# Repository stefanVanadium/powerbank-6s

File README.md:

# powerbank-6s

A serious DIY power bank built around **six removable 18650 cells**. It's meant to last for years and charge a phone as fast as the wall charger does.

<p align="center"><sub>158.6 × 142.6 × 39.2 mm, milled 6061 aluminium with a polished front edge and a glass front: Qi2 ring and colour display under the glass, cell door with laser marking on the back.</sub></p>

## PCB Preview (4-Layer, 152 × 136 mm)

| Top — Power, PD/PPS, BMS & MCU | Bottom — 6× Removable 18650 Holders |
|---|---|
|  |  |

## Highlights

- **45W Super Fast Charging 2.0** for the Galaxy S24+ (USB PD 3.0 PPS), and **65W** for laptops
- **3x USB-C + 2x USB-A**. Each USB-C port has its own converter, so all of them work at full speed at the same time
- **Removable cells (6S1P)**: insert cells at any voltage, the BMS balances them, and you can pull them out fully charged
- **Pass-through charging**: one wall charger fills the pack and your phone overnight
- **Solar input**: plug a foldable USB-C panel into C1 (the charger tracks the panel's maximum power point)
- **Magnetic Qi2 wireless** charging under the glass front
- **Color display** showing every cell's voltage, watts in/out per port, and which slot has a problem
- **Real 6S BMS** with per-cell protection and balancing

## Enclosure (v1 model)

<p align="center"><sub>Rendered in Blender from the real model: the case parts from <code>enclosure/case.py</code> and the routed board exported from KiCad (<code>enclosure/blender_scene.py</code>).</sub></p>

| Front: glass, Qi2 ring, display, buttons | Back: cell door, logo, feet, port labels |
|---|---|
|  |  |

- **158.6 × 142.6 × 39.2 mm**, milled 6061 aluminium body (~290 g) + 2.5 mm aluminium cell door (~145 g)
- **Glass front**: one 1.5 mm tempered glass, black inside, with a window for the display; the Qi2 coil sits right under it (wireless charging can't pass through aluminium)
- **Aluminium mid-frame under the glass** doubles as the heat sink: thermal pads carry the heat from the 12 converter MOSFETs and 4 inductors into the frame and the walls. The case is sealed, with no vents
- **Cell door**: 4 Torx screws into steel hex standoffs that also hold the board, so swapping cells never wears the aluminium threads. Cell polarity and slot numbers are engraved inside the door
- Port openings follow the connector datasheets, with recesses for the plug overmolds and engraved labels
- Model in [build123d](https://github.com/gumyr/build123d) (`enclosure/case.py`), collision check against the real board (`enclosure/check.py`, 0 collisions), FreeCAD file `enclosure/out/powerbank_case.FCStd`

## How it works

```
USB-C1  in/out  ── TPS25751S ── BQ25756 ──┐
USB-C2  out     ── TPS25751S ── BQ25756 ──┤
USB-C3  out     ── TPS25751S ── BQ25756 ──┼── 6S removable pack ── BQ76952 BMS
USB-A1/A2 5V    ── LM73605 ──────────────┤
Qi2 module 12V  ── LMR36520 ─────────────┤
STM32G071 + TFT ── LMR36506 ─────────────┘
```

Each USB-C port pairs a TI PD controller with a BQ25756 bidirectional buck-boost, which produces any voltage from 3.3 to 21V in 20mV steps. That fine control is what PPS needs. An STM32 handles the display, splits the power budget between ports, and decides when the pack is full.

Full architecture, BOM with JLCPCB stock/prices, cost estimate and the cell-testing procedure are in **[powerbank.md](powerbank.md)**.

## Specs (planned)

| | |
|---|---|
| Cells | 6x 18650 in series, removable (currently EVE ICR18650/26V) |
| Pack | 15–25.2V, ~55Wh with 2.55Ah cells, ~75Wh with 3.5Ah cells |
| USB-C | 3 ports, PD 3.0 + PPS, up to 65W each |
| USB-A | 2 ports, 5V / 2A, BC1.2 |
| Wireless | Qi2 15W (module) |
| Input | USB-C PD or solar panel on C1 |
| Total output | ~100W from the pack, shared between ports |

## Repo layout

```
powerbank.md          project documentation (start here)
connections.md        safety Wave 0, power tree, I2C map, MCU pinout
powerbank.kicad_*     KiCad 10 project (6 hierarchical sheets + 4-layer PCB)
enclosure/            case model (build123d), collision check, FreeCAD file, STEP for milling
images/               3D PCB and case renders
lib/                  symbols, footprints, 3D models (verified against datasheets)
datasheets/           datasheets for every chosen part
powerbank.tex/.pdf    printable writeup
```

## Status

- [x] Requirements, architecture, full BOM & Safety Wave 0
- [x] KiCad libraries + datasheets + footprint audit
- [x] Schematic (6 hierarchical sheets, 241 components, 0 ERC errors)
- [x] PCB (4-layer 152 × 136 mm, 0 DRC violations, 0 unconnected pads)
- [ ] Display FPC & Qi2 module finalization
- [ ] Firmware
- [x] Case v1 model (milled aluminium, glass front, FreeCAD)
- [ ] Case: measure the cell height in the holder, final Qi2 / display sizes, then milling

## License

[MIT](LICENSE) for the design files and documentation in this repo. Datasheets in `datasheets/` belong to their manufacturers. Footprints and 3D models in `lib/` were generated from EasyEDA/LCSC data.

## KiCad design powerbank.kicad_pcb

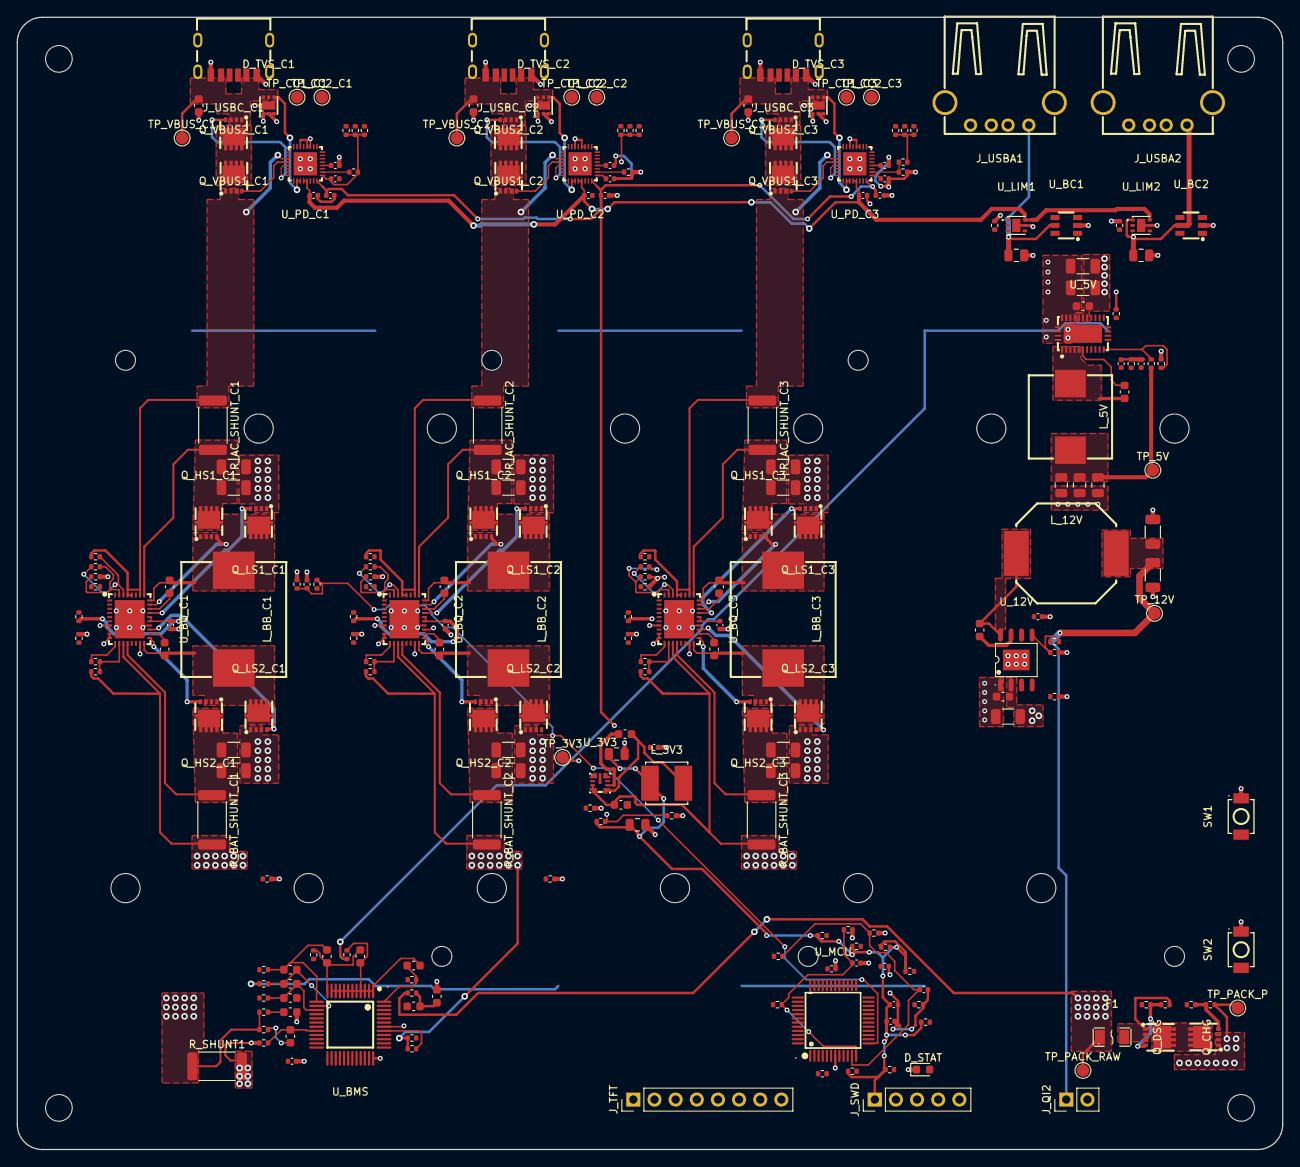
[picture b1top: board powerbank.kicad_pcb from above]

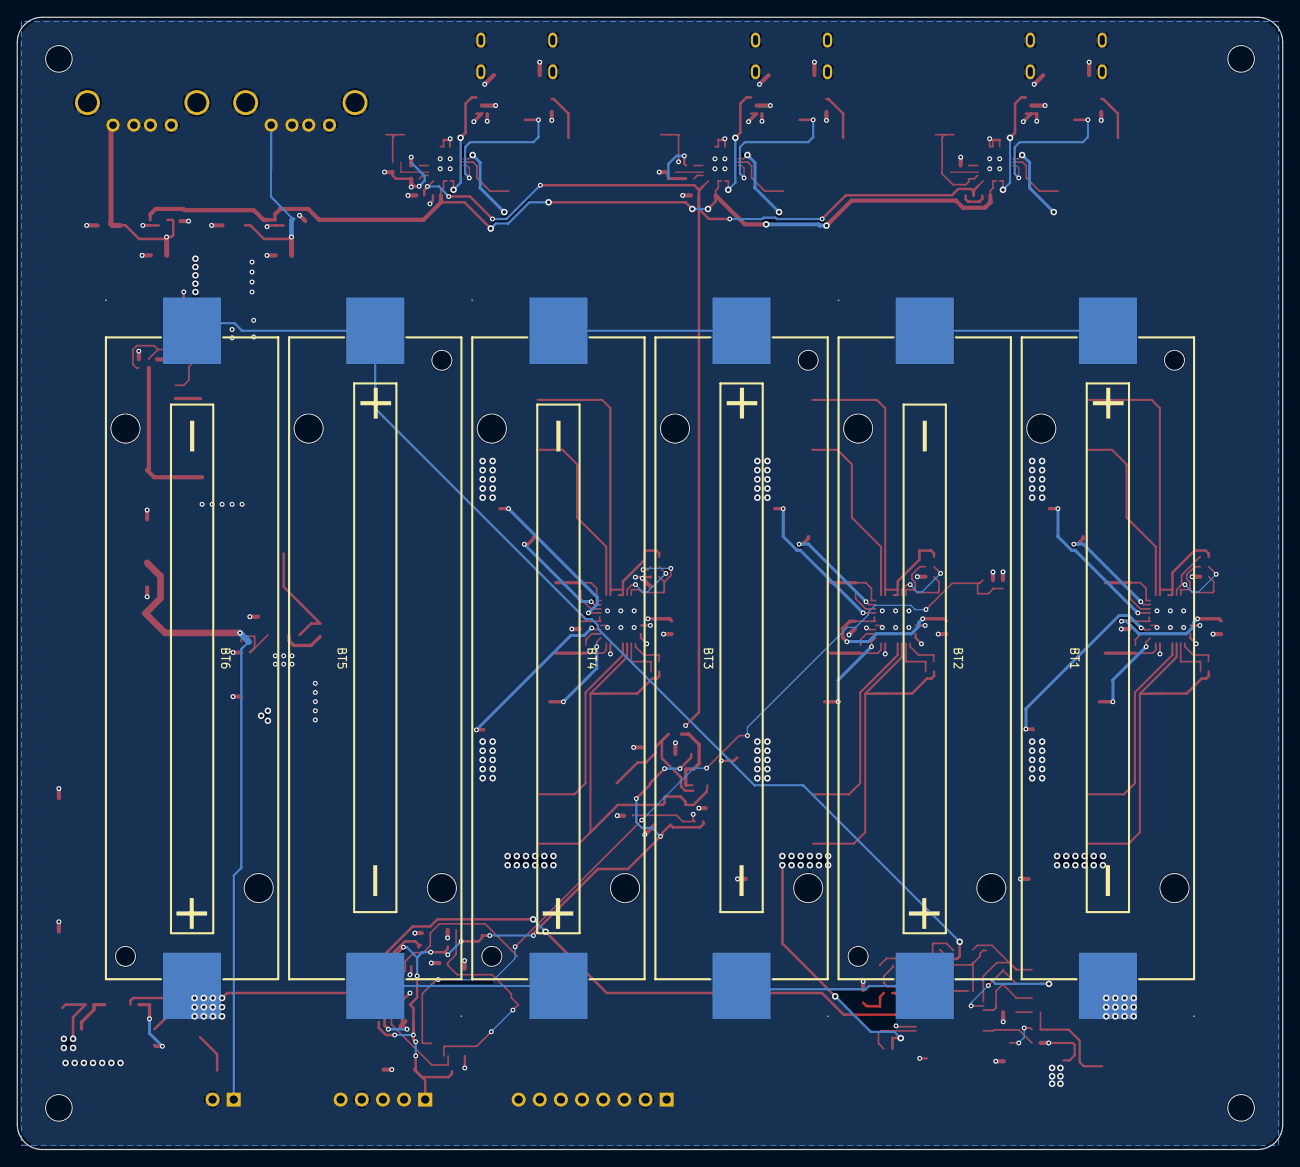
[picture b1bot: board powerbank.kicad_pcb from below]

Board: 4 copper layers, 152.0 x 136.0 mm, 245 parts (6 on the bottom side), 180 nets.

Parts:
BT1: 18650 Cell 1; BAT-SMD_1042P
BT2: 18650 Cell 2; BAT-SMD_1042P
BT3: 18650 Cell 3; BAT-SMD_1042P
BT4: 18650 Cell 4; BAT-SMD_1042P
BT5: 18650 Cell 5; BAT-SMD_1042P
BT6: 18650 Cell 6; BAT-SMD_1042P
C_3V3_IN: 4.7uF 50V; C_0603_1608Metric
C_3V3_OUT1, C_3V3_OUT2, C_5V_OUT1, C_5V_OUT2, C_5V_OUT3: 22uF 16V; C_0805_2012Metric
C_5V_IN1, C_5V_IN2, C_12V_IN1: 10uF 35V; C_1206_3216Metric
C_5V_IN3, C_12V_IN2: 100nF 50V; C_0603_1608Metric
C_12V_OUT1, C_12V_OUT2: 22uF 25V; C_1206_3216Metric
C_BAT: 1uF 50V; C_0603_1608Metric
C_BOOT_3V3, C_BOOT_5V, C_BOOT_12V: 100nF 50V; C_0603_1608Metric
C_BTST1_C1, C_BTST1_C2, C_BTST1_C3, C_BTST2_C1, C_BTST2_C2, C_BTST2_C3: 100nF 50V; C_0603_1608Metric
C_CP1: 470nF 50V; C_0603_1608Metric
C_LDO1V5_C1, C_LDO1V5_C2, C_LDO1V5_C3, C_LDO3V3_C1, C_LDO3V3_C2, C_LDO3V3_C3: 2.2uF 16V; C_0402_1005Metric
C_MCU1: 100nF; C_0402_1005Metric
C_MCU2: 4.7uF 16V; C_0402_1005Metric
C_NRST: 100nF; C_0402_1005Metric
C_NTC_C1: 100nF; C_0402_1005Metric
C_NTC_PWR: 100nF; C_0402_1005Metric
C_NTC_QI2: 100nF; C_0402_1005Metric
C_PP5V_C1, C_PP5V_C2, C_PP5V_C3: 4.7uF 16V; C_0402_1005Metric
C_REG18: 2.2uF 16V; C_0402_1005Metric
C_REGN_C1, C_REGN_C2, C_REGN_C3: 4.7uF 16V; C_0402_1005Metric
C_SR: 100nF 50V; C_0603_1608Metric
C_SS_5V: 100nF; C_0402_1005Metric
C_USBA1, C_USBA2: 22uF 16V; C_0805_2012Metric
C_VAC1_C1, C_VAC1_C2, C_VAC1_C3, C_VAC2_C1, C_VAC2_C2, C_VAC2_C3: 10uF 35V; C_1206_3216Metric
C_VBAT1_C1, C_VBAT1_C2, C_VBAT1_C3, C_VBAT2_C1, C_VBAT2_C2, C_VBAT2_C3: 10uF 35V; C_1206_3216Metric
C_VBUS_ESD_C1, C_VBUS_ESD_C2, C_VBUS_ESD_C3: 1uF 50V; C_0603_1608Metric
C_VC0, C_VC1, C_VC2, C_VC3, C_VC4, C_VC5, C_VC16: 220nF 50V; C_0603_1608Metric
C_VCC_3V3, C_VCC_12V: 1uF 16V; C_0402_1005Metric
C_VCC_5V: 2.2uF 16V; C_0402_1005Metric
C_VIN3V3_C1, C_VIN3V3_C2, C_VIN3V3_C3: 100nF; C_0402_1005Metric
C_VREF: 100nF; C_0402_1005Metric
D_STAT: Green; LED_0603_1608Metric
D_TVS_C1, D_TVS_C2, D_TVS_C3: TVS2200DRVR; WSON-6_L2.0-W2.0-P0.65-BL-EP
F1: 15A 35V; F1206
H1, H2, H3, H4: M3; MountingHole_3.2mm_M3
J_QI2: Qi2 12V Power; PinHeader_1x02_P2.54mm_Vertical
J_SWD: SWD; PinHeader_1x05_P2.54mm_Vertical
J_TFT: TFT ST7789 SPI; PinHeader_1x08_P2.54mm_Vertical
J_USBA1, J_USBA2: BX-TYPE-A-MWC4P; USB-A-TH_UB20A2-04R068-WPP-DF
J_USBC_C1, J_USBC_C2, J_USBC_C3: TYPE-C-31-M-17; USB-C-SMD_10P-P1.00-L6.8-W8.9
L_3V3: 15uH 2.3A; IND-SMD_L5.0-W5.0
L_5V: 4.7uH 17A; IND-SMD_L10.0-W10.0_CLF10060NIT
L_12V: 33uH 4.25A; IND-SMD_L12.0-W12.0_CDRH129RNP-330MC
L_BB_C1, L_BB_C2, L_BB_C3: 10uH 15.5A; IND-SMD_L13.8-W12.6_MHCC12050
Q_CHG: TPN2R304PL; TSON-8_L3.1-W3.1-P0.65-LS3.3-BL-EP
Q_DSG: TPN2R304PL; TSON-8_L3.1-W3.1-P0.65-LS3.3-BL-EP
Q_HS1_C1, Q_HS1_C2, Q_HS1_C3, Q_HS2_C1, Q_HS2_C2, Q_HS2_C3: TPN2R304PL; TSON-8_L3.1-W3.1-P0.65-LS3.3-BL-EP
Q_LS1_C1, Q_LS1_C2, Q_LS1_C3, Q_LS2_C1, Q_LS2_C2, Q_LS2_C3: TPN2R304PL; TSON-8_L3.1-W3.1-P0.65-LS3.3-BL-EP
Q_VBUS1_C1, Q_VBUS1_C2, Q_VBUS1_C3, Q_VBUS2_C1, Q_VBUS2_C2, Q_VBUS2_C3: TPN2R304PL; TSON-8_L3.1-W3.1-P0.65-LS3.3-BL-EP
R_ACOV_B_C1, R_ACOV_B_C2, R_ACOV_B_C3: 4.7k; R_0402_1005Metric
R_ACOV_M_C1, R_ACOV_M_C2, R_ACOV_M_C3: 27k; R_0402_1005Metric
R_ACOV_T_C1, R_ACOV_T_C2, R_ACOV_T_C3: 100k; R_0402_1005Metric
R_AC_SHUNT_C1, R_AC_SHUNT_C2, R_AC_SHUNT_C3: 2m; R_2512_6332Metric
R_ALERT: 10k; R_0402_1005Metric
R_BAT: 100; R_0402_1005Metric
R_BAT_SHUNT_C1, R_BAT_SHUNT_C2, R_BAT_SHUNT_C3: 5m; R_2512_6332Metric
R_BOOT0: 10k; R_0402_1005Metric
R_C1_AD1, R_C2_AD1: 10k; R_0402_1005Metric
R_C3_AD1_B: 100k; R_0402_1005Metric
R_C3_AD1_T: 24.9k; R_0402_1005Metric
R_CHG_G: 100; R_0402_1005Metric
R_CHG_GS: 1M; R_0402_1005Metric
R_DSG_G: 100; R_0402_1005Metric
R_DSG_GS: 1M; R_0402_1005Metric
R_EN_5V_PD, R_EN_12V_PD: 100k; R_0402_1005Metric
R_FB_3V3_B: 43.2k; R_0402_1005Metric
R_FB_3V3_T, R_FB_5V_T, R_FB_12V_T: 100k; R_0402_1005Metric
R_FB_5V_B: 24.9k; R_0402_1005Metric
R_FB_12V_B: 9.09k; R_0402_1005Metric
R_FB_B_C1, R_FB_B_C2, R_FB_B_C3: 16.2k; R_0402_1005Metric
R_FB_T_C1, R_FB_T_C2, R_FB_T_C3: 249k; R_0402_1005Metric
R_FSW_C1, R_FSW_C2, R_FSW_C3: 24.9k; R_0402_1005Metric
R_I2C1_SCL, R_I2C1_SDA, R_I2CC_SCL_C1, R_I2CC_SCL_C2, R_I2CC_SCL_C3, R_I2CC_SDA_C1, R_I2CC_SDA_C2, R_I2CC_SDA_C3: 4.7k; R_0402_1005Metric
R_I2CC_IRQ_C1, R_I2CC_IRQ_C2, R_I2CC_IRQ_C3: 10k; R_0402_1005Metric
R_ILIM1, R_ILIM2: 49.9k; R_0402_1005Metric
R_IRQ1, R_IRQ2, R_IRQ3: 10k; R_0402_1005Metric
R_LD: 10k; R_0402_1005Metric
R_LED: 1k; R_0402_1005Metric
R_NTC_C1: 10k; R_0402_1005Metric
R_NTC_PWR: 10k; R_0402_1005Metric
R_NTC_QI2: 10k; R_0402_1005Metric
R_PACK: 10k; R_0402_1005Metric
R_RT_3V3: 15.4k; R_0402_1005Metric
R_RT_5V: 78.7k; R_0402_1005Metric
R_SHUNT1: 1m; R_2512_6332Metric
R_SRN: 100; R_0402_1005Metric
R_SRP: 100; R_0402_1005Metric
R_TS_B_C1, R_TS_B_C2, R_TS_B_C3: 10k; R_0402_1005Metric
R_TS_T_C1, R_TS_T_C2, R_TS_T_C3: 10k; R_0402_1005Metric
R_VC0, R_VC1, R_VC2, R_VC3, R_VC4, R_VC5, R_VC16: 20; R_0402_1005Metric
R_VREF: 20; R_0402_1005Metric
SW1: BTN_1; SW-SMD_L3.9-W3.0-P4.45
SW2: BTN_2; SW-SMD_L3.9-W3.0-P4.45
TH_C1: 10k NTC; R_0402_1005Metric
TH_PACK1, TH_PACK2: 10k NTC; R_0402_1005Metric
TH_PWR: 10k NTC; R_0402_1005Metric
TH_QI2: 10k NTC; R_0402_1005Metric
TP_3V3: 3V3; TestPoint_Pad_D1.5mm
TP_5V: 5V_RAIL; TestPoint_Pad_D1.5mm
TP_12V: 12V_QI2; TestPoint_Pad_D1.5mm
TP_CC1_C1, TP_CC1_C2, TP_CC1_C3: CC1; TestPoint_Pad_D1.5mm
TP_CC2_C1, TP_CC2_C2, TP_CC2_C3: CC2; TestPoint_Pad_D1.5mm
TP_PACK_P: PACK_P; TestPoint_Pad_D1.5mm
TP_PACK_RAW: PACK_RAW_P; TestPoint_Pad_D1.5mm
TP_VBUS_C1, TP_VBUS_C2, TP_VBUS_C3: VBUS_CONN; TestPoint_Pad_D1.5mm
U_3V3: LMR36506RRPER; VQFN-9_L2.0-W2.0-P0.50-TL
U_5V: LM73605RNPR; WQFN-30_L6.0-W4.0-P0.50-BL-EP
U_12V: LMR36520ADDAR; POWERPAD-SO-8_L4.9-W3.9-P1.27-LS6.0-BL-EP
U_BC1, U_BC2: TPS2514DBVR; SOT-23-6_L2.9-W1.6-P0.95-LS2.8-BR
U_BMS: BQ76952PFBR; TQFP-48_L7.0-W7.0-P0.50-LS9.0-BL
U_BQ_C1, U_BQ_C2, U_BQ_C3: BQ25756RRVR; TQFN-36_L6.0-W5.0-P0.50-BL-EP-1
U_LIM1, U_LIM2: TPS25200DRVR; WSON-6_L2.0-W2.0-P0.65-TL-EP
U_MCU: STM32G071CBT6; LQFP-48_L7.0-W7.0-P0.50-LS9.0-BL
U_PD_C1, U_PD_C2, U_PD_C3: TPS25751SRSMR; QFN-32_L4.0-W4.0-P0.40-TL-EP2.8

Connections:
/3V3: C_3V3_OUT1.1, C_3V3_OUT2.1, C_MCU1.1, C_MCU2.1, C_VIN3V3_C1.1, C_VIN3V3_C2.1, C_VIN3V3_C3.1, J_SWD.1, J_TFT.1, L_3V3.2, R_ALERT.1, R_FB_3V3_T.1, R_I2C1_SCL.1, R_I2C1_SDA.1, R_IRQ1.1, R_IRQ2.1, R_IRQ3.1, R_VREF.1, TP_3V3.1, U_MCU.4, U_MCU.6, U_PD_C1.32, U_PD_C2.32, U_PD_C3.32
/5V_RAIL: C_5V_OUT1.1, C_5V_OUT2.1, C_5V_OUT3.1, C_PP5V_C1.1, C_PP5V_C2.1, C_PP5V_C3.1, L_5V.2, R_FB_5V_T.1, TP_5V.1, U_5V.8, U_LIM1.6, U_LIM2.6, U_PD_C1.28, U_PD_C1.29, U_PD_C2.28, U_PD_C2.29, U_PD_C3.28, U_PD_C3.29
/BMS_6S/BAT_NEG: BT1.1, R_SHUNT1.1, R_SRP.1, R_VC0.1
/BMS_6S/BMS_BAT: C_BAT.1, C_CP1.2, R_BAT.2, U_BMS.47
/BMS_6S/BMS_CHG: R_CHG_G.1, U_BMS.45
/BMS_6S/BMS_CHG_G: Q_CHG.4, R_CHG_G.2, R_CHG_GS.1
/BMS_6S/BMS_CP1: C_CP1.1, U_BMS.46
/BMS_6S/BMS_DSG: R_DSG_G.1, U_BMS.43
/BMS_6S/BMS_DSG_G: Q_DSG.4, R_DSG_G.2, R_DSG_GS.1
/BMS_6S/BMS_LD_SENSE: R_LD.2, U_BMS.41
/BMS_6S/BMS_PACK_SENSE: R_PACK.2, U_BMS.42
/BMS_6S/BMS_REG18: C_REG18.1, U_BMS.24
/BMS_6S/BMS_SRN: C_SR.2, R_SRN.2, U_BMS.20
/BMS_6S/BMS_SRP: C_SR.1, R_SRP.2, U_BMS.18
/BMS_6S/BMS_TS1: TH_PACK1.1, U_BMS.21
/BMS_6S/BMS_TS3: TH_PACK2.1, U_BMS.23
/BMS_6S/CELL1_P: BT1.2, BT2.1, R_VC1.1
/BMS_6S/CELL2_P: BT2.2, BT3.1, R_VC2.1
/BMS_6S/CELL3_P: BT3.2, BT4.1, R_VC3.1
/BMS_6S/CELL4_P: BT4.2, BT5.1, R_VC4.1
/BMS_6S/CELL5_P: BT5.2, BT6.1, R_VC5.1
/BMS_6S/PACK_FUSED: F1.2, Q_CHG.1, Q_CHG.2, Q_CHG.3, R_CHG_GS.2
/BMS_6S/PACK_MID: Q_CHG.5, Q_DSG.5
/BMS_6S/PACK_RAW_P: BT6.2, F1.1, R_BAT.1, R_VC16.1, TP_PACK_RAW.1
/BMS_6S/VC0_F: C_VC0.1, C_VC1.2, R_VC0.2, U_BMS.16
/BMS_6S/VC1_F: C_VC1.1, C_VC2.2, R_VC1.2, U_BMS.15
/BMS_6S/VC2_F: C_VC2.1, C_VC3.2, R_VC2.2, U_BMS.14
/BMS_6S/VC3_F: C_VC3.1, C_VC4.2, R_VC3.2, U_BMS.13
/BMS_6S/VC4_F: C_VC4.1, C_VC5.2, R_VC4.2, U_BMS.12
/BMS_6S/VC5_F: C_VC5.1, C_VC16.2, R_VC5.2, U_BMS.1, U_BMS.2, U_BMS.3, U_BMS.4, U_BMS.5, U_BMS.6, U_BMS.7, U_BMS.8, U_BMS.9, U_BMS.10, U_BMS.11
/BMS_6S/VC16_F: C_VC16.1, R_VC16.2, U_BMS.48
/BMS_ALERT: R_ALERT.2, U_BMS.25, U_MCU.34
/BMS_CFETOFF: U_BMS.29, U_MCU.27
/BMS_DFETOFF: U_BMS.30, U_MCU.26
/BMS_RST_SHUT: U_BMS.33, U_MCU.28
/BUCK_5V_USBA/CBOOT_5V: C_BOOT_5V.1, U_5V.6
/BUCK_5V_USBA/FB_5V: R_FB_5V_B.1, R_FB_5V_T.2, U_5V.11
/BUCK_5V_USBA/ILIM_A1: R_ILIM1.1, U_LIM1.2
/BUCK_5V_USBA/ILIM_A2: R_ILIM2.1, U_LIM2.2
/BUCK_5V_USBA/RT_5V: R_RT_5V.1, U_5V.9
/BUCK_5V_USBA/SS_5V: C_SS_5V.1, U_5V.10
/BUCK_5V_USBA/SW_5V: C_BOOT_5V.2, L_5V.1, U_5V.1, U_5V.2, U_5V.3, U_5V.4, U_5V.5
/BUCK_5V_USBA/USBA1_DM: J_USBA1.2, U_BC1.6
/BUCK_5V_USBA/USBA1_DP: J_USBA1.3, U_BC1.1
/BUCK_5V_USBA/USBA2_DM: J_USBA2.2, U_BC2.6
/BUCK_5V_USBA/USBA2_DP: J_USBA2.3, U_BC2.1
/BUCK_5V_USBA/VBUS_A1: C_USBA1.1, J_USBA1.1, U_BC1.5, U_LIM1.1
/BUCK_5V_USBA/VBUS_A2: C_USBA2.1, J_USBA2.1, U_BC2.5, U_LIM2.1
/BUCK_5V_USBA/VCC_5V: C_VCC_5V.1, U_5V.7
/BUCK_12V_QI2/12V_QI2: C_12V_OUT1.1, C_12V_OUT2.1, J_QI2.1, L_12V.2, R_FB_12V_T.1, TP_12V.1
/BUCK_12V_QI2/BOOT_12V: C_BOOT_12V.1, U_12V.7
/BUCK_12V_QI2/FB_12V: R_FB_12V_B.1, R_FB_12V_T.2, U_12V.5
/BUCK_12V_QI2/SW_12V: C_BOOT_12V.2, L_12V.1, U_12V.8
/BUCK_12V_QI2/VCC_12V: C_VCC_12V.1, U_12V.6
/C1_ADCIN1: R_C1_AD1.2, U_PD_C1.2
/C1_LDO3V3: C_LDO3V3_C1.1, R_C1_AD1.1, R_I2CC_IRQ_C1.1, R_I2CC_SCL_C1.1, R_I2CC_SDA_C1.1, U_PD_C1.1
/C2_ADCIN1: R_C2_AD1.1, U_PD_C2.2
/C3_ADCIN1: R_C3_AD1_B.1, R_C3_AD1_T.2, U_PD_C3.2
/C3_LDO3V3: C_LDO3V3_C3.1, R_C3_AD1_T.1, R_I2CC_IRQ_C3.1, R_I2CC_SCL_C3.1, R_I2CC_SDA_C3.1, U_PD_C3.1
/EN_5V: R_EN_5V_PD.1, U_5V.18, U_MCU.20
/EN_12V: R_EN_12V_PD.1, U_12V.3, U_MCU.21
/I2C1_SCL: R_I2C1_SCL.2, U_BMS.26, U_MCU.45, U_PD_C1.9, U_PD_C2.9, U_PD_C3.9
/I2C1_SDA: R_I2C1_SDA.2, U_BMS.27, U_MCU.46, U_PD_C1.8, U_PD_C2.8, U_PD_C3.8
/MCU_UI/3V3_ANA: C_VREF.1, R_NTC_C1.1, R_NTC_PWR.1, R_NTC_QI2.1, R_VREF.2, U_MCU.5
/MCU_UI/ADC_NTC_C1: C_NTC_C1.1, R_NTC_C1.2, TH_C1.1, U_MCU.13
/MCU_UI/ADC_NTC_PWR: C_NTC_PWR.1, R_NTC_PWR.2, TH_PWR.1, U_MCU.12
/MCU_UI/ADC_NTC_QI2: C_NTC_QI2.1, R_NTC_QI2.2, TH_QI2.1, U_MCU.11
/MCU_UI/BOOT_3V3: C_BOOT_3V3.1, U_3V3.6
/MCU_UI/BTN_1: SW1.1, U_MCU.42
/MCU_UI/BTN_2: SW2.1, U_MCU.43
/MCU_UI/FB_3V3: R_FB_3V3_B.1, R_FB_3V3_T.2, U_3V3.8
/MCU_UI/LED_A: D_STAT.2, R_LED.2
/MCU_UI/LED_STATUS: R_LED.1, U_MCU.47
/MCU_UI/MCU_NRST: C_NRST.1, J_SWD.5, U_MCU.10
/MCU_UI/RT_3V3: R_RT_3V3.1, U_3V3.1
/MCU_UI/SWCLK: J_SWD.3, R_BOOT0.1, U_MCU.36
/MCU_UI/SWDIO: J_SWD.2, U_MCU.35
/MCU_UI/SW_3V3: C_BOOT_3V3.2, L_3V3.1, U_3V3.5
/MCU_UI/TFT_BLK: J_TFT.8, U_MCU.14
/MCU_UI/TFT_CS: J_TFT.7, U_MCU.15
/MCU_UI/TFT_DC: J_TFT.6, U_MCU.17
/MCU_UI/TFT_MOSI: J_TFT.4, U_MCU.18
/MCU_UI/TFT_RST: J_TFT.5, U_MCU.19
/MCU_UI/TFT_SCK: J_TFT.3, U_MCU.16
/MCU_UI/VCC_3V3: C_VCC_3V3.1, U_3V3.7
/PACK_P: C_3V3_IN.1, C_5V_IN1.1, C_5V_IN2.1, C_5V_IN3.1, C_12V_IN1.1, C_12V_IN2.1, Q_DSG.1, Q_DSG.2, Q_DSG.3, R_BAT_SHUNT_C1.2, R_BAT_SHUNT_C2.2, R_BAT_SHUNT_C3.2, R_DSG_GS.2, R_FB_T_C1.1, R_FB_T_C2.1, R_FB_T_C3.1, R_LD.1, R_PACK.1, TP_PACK_P.1, U_3V3.3, U_3V3.4, U_5V.20, U_5V.21, U_5V.22, U_12V.2, U_BQ_C1.13, U_BQ_C2.13, U_BQ_C3.13
/PD_C1_IRQ: R_IRQ1.2, U_MCU.29, U_PD_C1.10
/PD_C2_IRQ: R_IRQ2.2, U_MCU.32, U_PD_C2.10
/PD_C3_IRQ: R_IRQ3.2, U_MCU.33, U_PD_C3.10
/PG_5V: U_5V.16, U_MCU.48
/USBA1_EN: U_LIM1.4, U_MCU.22
/USBA1_FLT: U_LIM1.3, U_MCU.24
/USBA2_EN: U_LIM2.4, U_MCU.23
/USBA2_FLT: U_LIM2.3, U_MCU.25
/USB_C1_DRP_0x20/BQ_ACOV: R_ACOV_B_C1.1, R_ACOV_M_C1.2, U_BQ_C1.35
/USB_C1_DRP_0x20/BQ_ACUV: R_ACOV_M_C1.1, R_ACOV_T_C1.2, U_BQ_C1.34
/USB_C1_DRP_0x20/BQ_FB: R_FB_B_C1.1, R_FB_T_C1.2, U_BQ_C1.12
/USB_C1_DRP_0x20/BQ_FBG: R_FB_B_C1.2, U_BQ_C1.11
/USB_C1_DRP_0x20/BQ_FSW: R_FSW_C1.1, U_BQ_C1.36
/USB_C1_DRP_0x20/BQ_REGN: C_REGN_C1.1, R_TS_T_C1.1, U_BQ_C1.23, U_BQ_C1.24
/USB_C1_DRP_0x20/BQ_TS: R_TS_B_C1.1, R_TS_T_C1.2, U_BQ_C1.8
/USB_C1_DRP_0x20/BTST1: C_BTST1_C1.1, U_BQ_C1.26
/USB_C1_DRP_0x20/BTST2: C_BTST2_C1.1, U_BQ_C1.20
/USB_C1_DRP_0x20/CC1: J_USBC_C1.3, TP_CC1_C1.1, U_PD_C1.24
/USB_C1_DRP_0x20/CC2: J_USBC_C1.4, TP_CC2_C1.1, U_PD_C1.25
/USB_C1_DRP_0x20/GATE_VBUS: Q_VBUS1_C1.4, U_PD_C1.21
/USB_C1_DRP_0x20/GATE_VSYS: Q_VBUS2_C1.4, U_PD_C1.20
/USB_C1_DRP_0x20/HIDRV1: Q_HS1_C1.4, U_BQ_C1.27
/USB_C1_DRP_0x20/HIDRV2: Q_HS2_C1.4, U_BQ_C1.19
/USB_C1_DRP_0x20/I2CC_IRQ: R_I2CC_IRQ_C1.2, U_BQ_C1.3, U_PD_C1.17
/USB_C1_DRP_0x20/I2CC_SCL: R_I2CC_SCL_C1.2, U_BQ_C1.1, U_PD_C1.16
/USB_C1_DRP_0x20/I2CC_SDA: R_I2CC_SDA_C1.2, U_BQ_C1.2, U_PD_C1.15
/USB_C1_DRP_0x20/LDO_1V5: C_LDO1V5_C1.1, U_PD_C1.4
/USB_C1_DRP_0x20/LODRV1: Q_LS1_C1.4, U_BQ_C1.25
/USB_C1_DRP_0x20/LODRV2: Q_LS2_C1.4, U_BQ_C1.21
/USB_C1_DRP_0x20/SW1: C_BTST1_C1.2, L_BB_C1.1, Q_HS1_C1.1, Q_HS1_C1.2, Q_HS1_C1.3, Q_LS1_C1.5, U_BQ_C1.28
/USB_C1_DRP_0x20/SW2: C_BTST2_C1.2, L_BB_C1.2, Q_HS2_C1.1, Q_HS2_C1.2, Q_HS2_C1.3, Q_LS2_C1.5, U_BQ_C1.18
/USB_C1_DRP_0x20/VAC_BUS: Q_VBUS2_C1.1, Q_VBUS2_C1.2, Q_VBUS2_C1.3, R_ACOV_T_C1.1, R_AC_SHUNT_C1.1, U_BQ_C1.30, U_BQ_C1.32, U_BQ_C1.33, U_PD_C1.19
/USB_C1_DRP_0x20/VAC_STAGE: C_VAC1_C1.1, C_VAC2_C1.1, Q_HS1_C1.5, R_AC_SHUNT_C1.2, U_BQ_C1.29
/USB_C1_DRP_0x20/VBAT_STAGE: C_VBAT1_C1.1, C_VBAT2_C1.1, Q_HS2_C1.5, R_BAT_SHUNT_C1.1, U_BQ_C1.14
/USB_C1_DRP_0x20/VBUS_CONN: C_VBUS_ESD_C1.1, D_TVS_C1.4, D_TVS_C1.5, D_TVS_C1.6, J_USBC_C1.2, J_USBC_C1.5, Q_VBUS1_C1.1, Q_VBUS1_C1.2, Q_VBUS1_C1.3, TP_VBUS_C1.1, U_PD_C1.26, U_PD_C1.27
/USB_C1_DRP_0x20/VBUS_MID: Q_VBUS1_C1.5, Q_VBUS2_C1.5
/USB_C2_SRC_0x21/BQ_ACOV: R_ACOV_B_C2.1, R_ACOV_M_C2.2, U_BQ_C2.35
/USB_C2_SRC_0x21/BQ_ACUV: R_ACOV_M_C2.1, R_ACOV_T_C2.2, U_BQ_C2.34
/USB_C2_SRC_0x21/BQ_FB: R_FB_B_C2.1, R_FB_T_C2.2, U_BQ_C2.12
/USB_C2_SRC_0x21/BQ_FBG: R_FB_B_C2.2, U_BQ_C2.11
/USB_C2_SRC_0x21/BQ_FSW: R_FSW_C2.1, U_BQ_C2.36
/USB_C2_SRC_0x21/BQ_REGN: C_REGN_C2.1, R_TS_T_C2.1, U_BQ_C2.23, U_BQ_C2.24
/USB_C2_SRC_0x21/BQ_TS: R_TS_B_C2.1, R_TS_T_C2.2, U_BQ_C2.8
/USB_C2_SRC_0x21/BTST1: C_BTST1_C2.1, U_BQ_C2.26
/USB_C2_SRC_0x21/BTST2: C_BTST2_C2.1, U_BQ_C2.20
/USB_C2_SRC_0x21/CC1: J_USBC_C2.3, TP_CC1_C2.1, U_PD_C2.24
/USB_C2_SRC_0x21/CC2: J_USBC_C2.4, TP_CC2_C2.1, U_PD_C2.25
/USB_C2_SRC_0x21/GATE_VBUS: Q_VBUS1_C2.4, U_PD_C2.21
/USB_C2_SRC_0x21/GATE_VSYS: Q_VBUS2_C2.4, U_PD_C2.20
/USB_C2_SRC_0x21/HIDRV1: Q_HS1_C2.4, U_BQ_C2.27
/USB_C2_SRC_0x21/HIDRV2: Q_HS2_C2.4, U_BQ_C2.19
/USB_C2_SRC_0x21/I2CC_IRQ: R_I2CC_IRQ_C2.2, U_BQ_C2.3, U_PD_C2.17
/USB_C2_SRC_0x21/I2CC_SCL: R_I2CC_SCL_C2.2, U_BQ_C2.1, U_PD_C2.16
/USB_C2_SRC_0x21/I2CC_SDA: R_I2CC_SDA_C2.2, U_BQ_C2.2, U_PD_C2.15
/USB_C2_SRC_0x21/LDO_1V5: C_LDO1V5_C2.1, U_PD_C2.4
/USB_C2_SRC_0x21/LDO_3V3: C_LDO3V3_C2.1, R_I2CC_IRQ_C2.1, R_I2CC_SCL_C2.1, R_I2CC_SDA_C2.1, U_PD_C2.1
/USB_C2_SRC_0x21/LODRV1: Q_LS1_C2.4, U_BQ_C2.25
/USB_C2_SRC_0x21/LODRV2: Q_LS2_C2.4, U_BQ_C2.21
/USB_C2_SRC_0x21/SW1: C_BTST1_C2.2, L_BB_C2.1, Q_HS1_C2.1, Q_HS1_C2.2, Q_HS1_C2.3, Q_LS1_C2.5, U_BQ_C2.28
/USB_C2_SRC_0x21/SW2: C_BTST2_C2.2, L_BB_C2.2, Q_HS2_C2.1, Q_HS2_C2.2, Q_HS2_C2.3, Q_LS2_C2.5, U_BQ_C2.18
/USB_C2_SRC_0x21/VAC_BUS: Q_VBUS2_C2.1, Q_VBUS2_C2.2, Q_VBUS2_C2.3, R_ACOV_T_C2.1, R_AC_SHUNT_C2.1, U_BQ_C2.30, U_BQ_C2.32, U_BQ_C2.33, U_PD_C2.19
/USB_C2_SRC_0x21/VAC_STAGE: C_VAC1_C2.1, C_VAC2_C2.1, Q_HS1_C2.5, R_AC_SHUNT_C2.2, U_BQ_C2.29
/USB_C2_SRC_0x21/VBAT_STAGE: C_VBAT1_C2.1, C_VBAT2_C2.1, Q_HS2_C2.5, R_BAT_SHUNT_C2.1, U_BQ_C2.14
/USB_C2_SRC_0x21/VBUS_CONN: C_VBUS_ESD_C2.1, D_TVS_C2.4, D_TVS_C2.5, D_TVS_C2.6, J_USBC_C2.2, J_USBC_C2.5, Q_VBUS1_C2.1, Q_VBUS1_C2.2, Q_VBUS1_C2.3, TP_VBUS_C2.1, U_PD_C2.26, U_PD_C2.27
/USB_C2_SRC_0x21/VBUS_MID: Q_VBUS1_C2.5, Q_VBUS2_C2.5
/USB_C3_SRC_0x22/BQ_ACOV: R_ACOV_B_C3.1, R_ACOV_M_C3.2, U_BQ_C3.35
/USB_C3_SRC_0x22/BQ_ACUV: R_ACOV_M_C3.1, R_ACOV_T_C3.2, U_BQ_C3.34
/USB_C3_SRC_0x22/BQ_FB: R_FB_B_C3.1, R_FB_T_C3.2, U_BQ_C3.12
/USB_C3_SRC_0x22/BQ_FBG: R_FB_B_C3.2, U_BQ_C3.11
/USB_C3_SRC_0x22/BQ_FSW: R_FSW_C3.1, U_BQ_C3.36
/USB_C3_SRC_0x22/BQ_REGN: C_REGN_C3.1, R_TS_T_C3.1, U_BQ_C3.23, U_BQ_C3.24
/USB_C3_SRC_0x22/BQ_TS: R_TS_B_C3.1, R_TS_T_C3.2, U_BQ_C3.8
/USB_C3_SRC_0x22/BTST1: C_BTST1_C3.1, U_BQ_C3.26
/USB_C3_SRC_0x22/BTST2: C_BTST2_C3.1, U_BQ_C3.20
/USB_C3_SRC_0x22/CC1: J_USBC_C3.3, TP_CC1_C3.1, U_PD_C3.24
/USB_C3_SRC_0x22/CC2: J_USBC_C3.4, TP_CC2_C3.1, U_PD_C3.25
/USB_C3_SRC_0x22/GATE_VBUS: Q_VBUS1_C3.4, U_PD_C3.21
/USB_C3_SRC_0x22/GATE_VSYS: Q_VBUS2_C3.4, U_PD_C3.20
/USB_C3_SRC_0x22/HIDRV1: Q_HS1_C3.4, U_BQ_C3.27
/USB_C3_SRC_0x22/HIDRV2: Q_HS2_C3.4, U_BQ_C3.19
/USB_C3_SRC_0x22/I2CC_IRQ: R_I2CC_IRQ_C3.2, U_BQ_C3.3, U_PD_C3.17
/USB_C3_SRC_0x22/I2CC_SCL: R_I2CC_SCL_C3.2, U_BQ_C3.1, U_PD_C3.16
/USB_C3_SRC_0x22/I2CC_SDA: R_I2CC_SDA_C3.2, U_BQ_C3.2, U_PD_C3.15
/USB_C3_SRC_0x22/LDO_1V5: C_LDO1V5_C3.1, U_PD_C3.4
/USB_C3_SRC_0x22/LODRV1: Q_LS1_C3.4, U_BQ_C3.25
/USB_C3_SRC_0x22/LODRV2: Q_LS2_C3.4, U_BQ_C3.21
/USB_C3_SRC_0x22/SW1: C_BTST1_C3.2, L_BB_C3.1, Q_HS1_C3.1, Q_HS1_C3.2, Q_HS1_C3.3, Q_LS1_C3.5, U_BQ_C3.28
/USB_C3_SRC_0x22/SW2: C_BTST2_C3.2, L_BB_C3.2, Q_HS2_C3.1, Q_HS2_C3.2, Q_HS2_C3.3, Q_LS2_C3.5, U_BQ_C3.18
/USB_C3_SRC_0x22/VAC_BUS: Q_VBUS2_C3.1, Q_VBUS2_C3.2, Q_VBUS2_C3.3, R_ACOV_T_C3.1, R_AC_SHUNT_C3.1, U_BQ_C3.30, U_BQ_C3.32, U_BQ_C3.33, U_PD_C3.19
/USB_C3_SRC_0x22/VAC_STAGE: C_VAC1_C3.1, C_VAC2_C3.1, Q_HS1_C3.5, R_AC_SHUNT_C3.2, U_BQ_C3.29
/USB_C3_SRC_0x22/VBAT_STAGE: C_VBAT1_C3.1, C_VBAT2_C3.1, Q_HS2_C3.5, R_BAT_SHUNT_C3.1, U_BQ_C3.14
/USB_C3_SRC_0x22/VBUS_CONN: C_VBUS_ESD_C3.1, D_TVS_C3.4, D_TVS_C3.5, D_TVS_C3.6, J_USBC_C3.2, J_USBC_C3.5, Q_VBUS1_C3.1, Q_VBUS1_C3.2, Q_VBUS1_C3.3, TP_VBUS_C3.1, U_PD_C3.26, U_PD_C3.27
/USB_C3_SRC_0x22/VBUS_MID: Q_VBUS1_C3.5, Q_VBUS2_C3.5
GND: C_3V3_IN.2, C_3V3_OUT1.2, C_3V3_OUT2.2, C_5V_IN1.2, C_5V_IN2.2, C_5V_IN3.2, C_5V_OUT1.2, C_5V_OUT2.2, C_5V_OUT3.2, C_12V_IN1.2, C_12V_IN2.2, C_12V_OUT1.2, C_12V_OUT2.2, C_BAT.2, C_LDO1V5_C1.2, C_LDO1V5_C2.2, C_LDO1V5_C3.2, C_LDO3V3_C1.2, C_LDO3V3_C2.2, C_LDO3V3_C3.2, C_MCU1.2, C_MCU2.2, C_NRST.2, C_NTC_C1.2, C_NTC_PWR.2, C_NTC_QI2.2, C_PP5V_C1.2, C_PP5V_C2.2, C_PP5V_C3.2, C_REG18.2, C_REGN_C1.2, C_REGN_C2.2, C_REGN_C3.2, C_SS_5V.2, C_USBA1.2, C_USBA2.2, C_VAC1_C1.2, C_VAC1_C2.2, C_VAC1_C3.2, C_VAC2_C1.2, C_VAC2_C2.2, C_VAC2_C3.2, C_VBAT1_C1.2, C_VBAT1_C2.2, C_VBAT1_C3.2, C_VBAT2_C1.2, C_VBAT2_C2.2, C_VBAT2_C3.2, C_VBUS_ESD_C1.2, C_VBUS_ESD_C2.2, C_VBUS_ESD_C3.2, C_VC0.2, C_VCC_3V3.2, C_VCC_5V.2, C_VCC_12V.2, C_VIN3V3_C1.2, C_VIN3V3_C2.2, C_VIN3V3_C3.2, C_VREF.2, D_STAT.1, D_TVS_C1.1, D_TVS_C1.2, D_TVS_C1.3, D_TVS_C1.7, D_TVS_C2.1, D_TVS_C2.2, D_TVS_C2.3, D_TVS_C2.7, D_TVS_C3.1, D_TVS_C3.2, D_TVS_C3.3, D_TVS_C3.7, J_QI2.2, J_SWD.4, J_TFT.2, J_USBA1.4, J_USBA1.5, J_USBA1.6, J_USBA2.4, J_USBA2.5, J_USBA2.6, J_USBC_C1.0, J_USBC_C1.1, J_USBC_C1.6, J_USBC_C2.0, J_USBC_C2.1, J_USBC_C2.6, J_USBC_C3.0, J_USBC_C3.1, J_USBC_C3.6, Q_LS1_C1.1, Q_LS1_C1.2, Q_LS1_C1.3, Q_LS1_C2.1, Q_LS1_C2.2, Q_LS1_C2.3, Q_LS1_C3.1, Q_LS1_C3.2, Q_LS1_C3.3, Q_LS2_C1.1, Q_LS2_C1.2, Q_LS2_C1.3, Q_LS2_C2.1, Q_LS2_C2.2, Q_LS2_C2.3, Q_LS2_C3.1, Q_LS2_C3.2, Q_LS2_C3.3, R_ACOV_B_C1.2, R_ACOV_B_C2.2, R_ACOV_B_C3.2, R_BOOT0.2, R_C2_AD1.2, R_C3_AD1_B.2, R_EN_5V_PD.2, R_EN_12V_PD.2, R_FB_3V3_B.2, R_FB_5V_B.2, R_FB_12V_B.2, R_FSW_C1.2, R_FSW_C2.2, R_FSW_C3.2, R_ILIM1.2, R_ILIM2.2, R_RT_3V3.2, R_RT_5V.2, R_SHUNT1.2, R_SRN.1, R_TS_B_C1.2, R_TS_B_C2.2, R_TS_B_C3.2, SW1.2, SW2.2, TH_C1.2, TH_PACK1.2, TH_PACK2.2, TH_PWR.2, TH_QI2.2, U_3V3.9, U_5V.17, U_5V.19, U_5V.23, U_5V.24, U_5V.25, U_5V.26, U_5V.31, U_12V.1, U_12V.9, U_BC1.2, U_BC2.2, U_BMS.17, U_BMS.36, U_BQ_C1.7, U_BQ_C1.9, U_BQ_C1.10, U_BQ_C1.17, U_BQ_C1.22, U_BQ_C1.37, U_BQ_C2.7, U_BQ_C2.9, U_BQ_C2.10, U_BQ_C2.17, U_BQ_C2.22, U_BQ_C2.37, U_BQ_C3.7, U_BQ_C3.9, U_BQ_C3.10, U_BQ_C3.17, U_BQ_C3.22, U_BQ_C3.37, U_LIM1.5, U_LIM1.7, U_LIM2.5, U_LIM2.7, U_MCU.7, U_PD_C1.3, U_PD_C1.11, U_PD_C1.12, U_PD_C1.14, U_PD_C1.33, U_PD_C2.3, U_PD_C2.11, U_PD_C2.12, U_PD_C2.14, U_PD_C2.33, U_PD_C3.3, U_PD_C3.11, U_PD_C3.12, U_PD_C3.14, U_PD_C3.33
